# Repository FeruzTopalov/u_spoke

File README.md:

# u_spoke
uSpoke - headless Spoke

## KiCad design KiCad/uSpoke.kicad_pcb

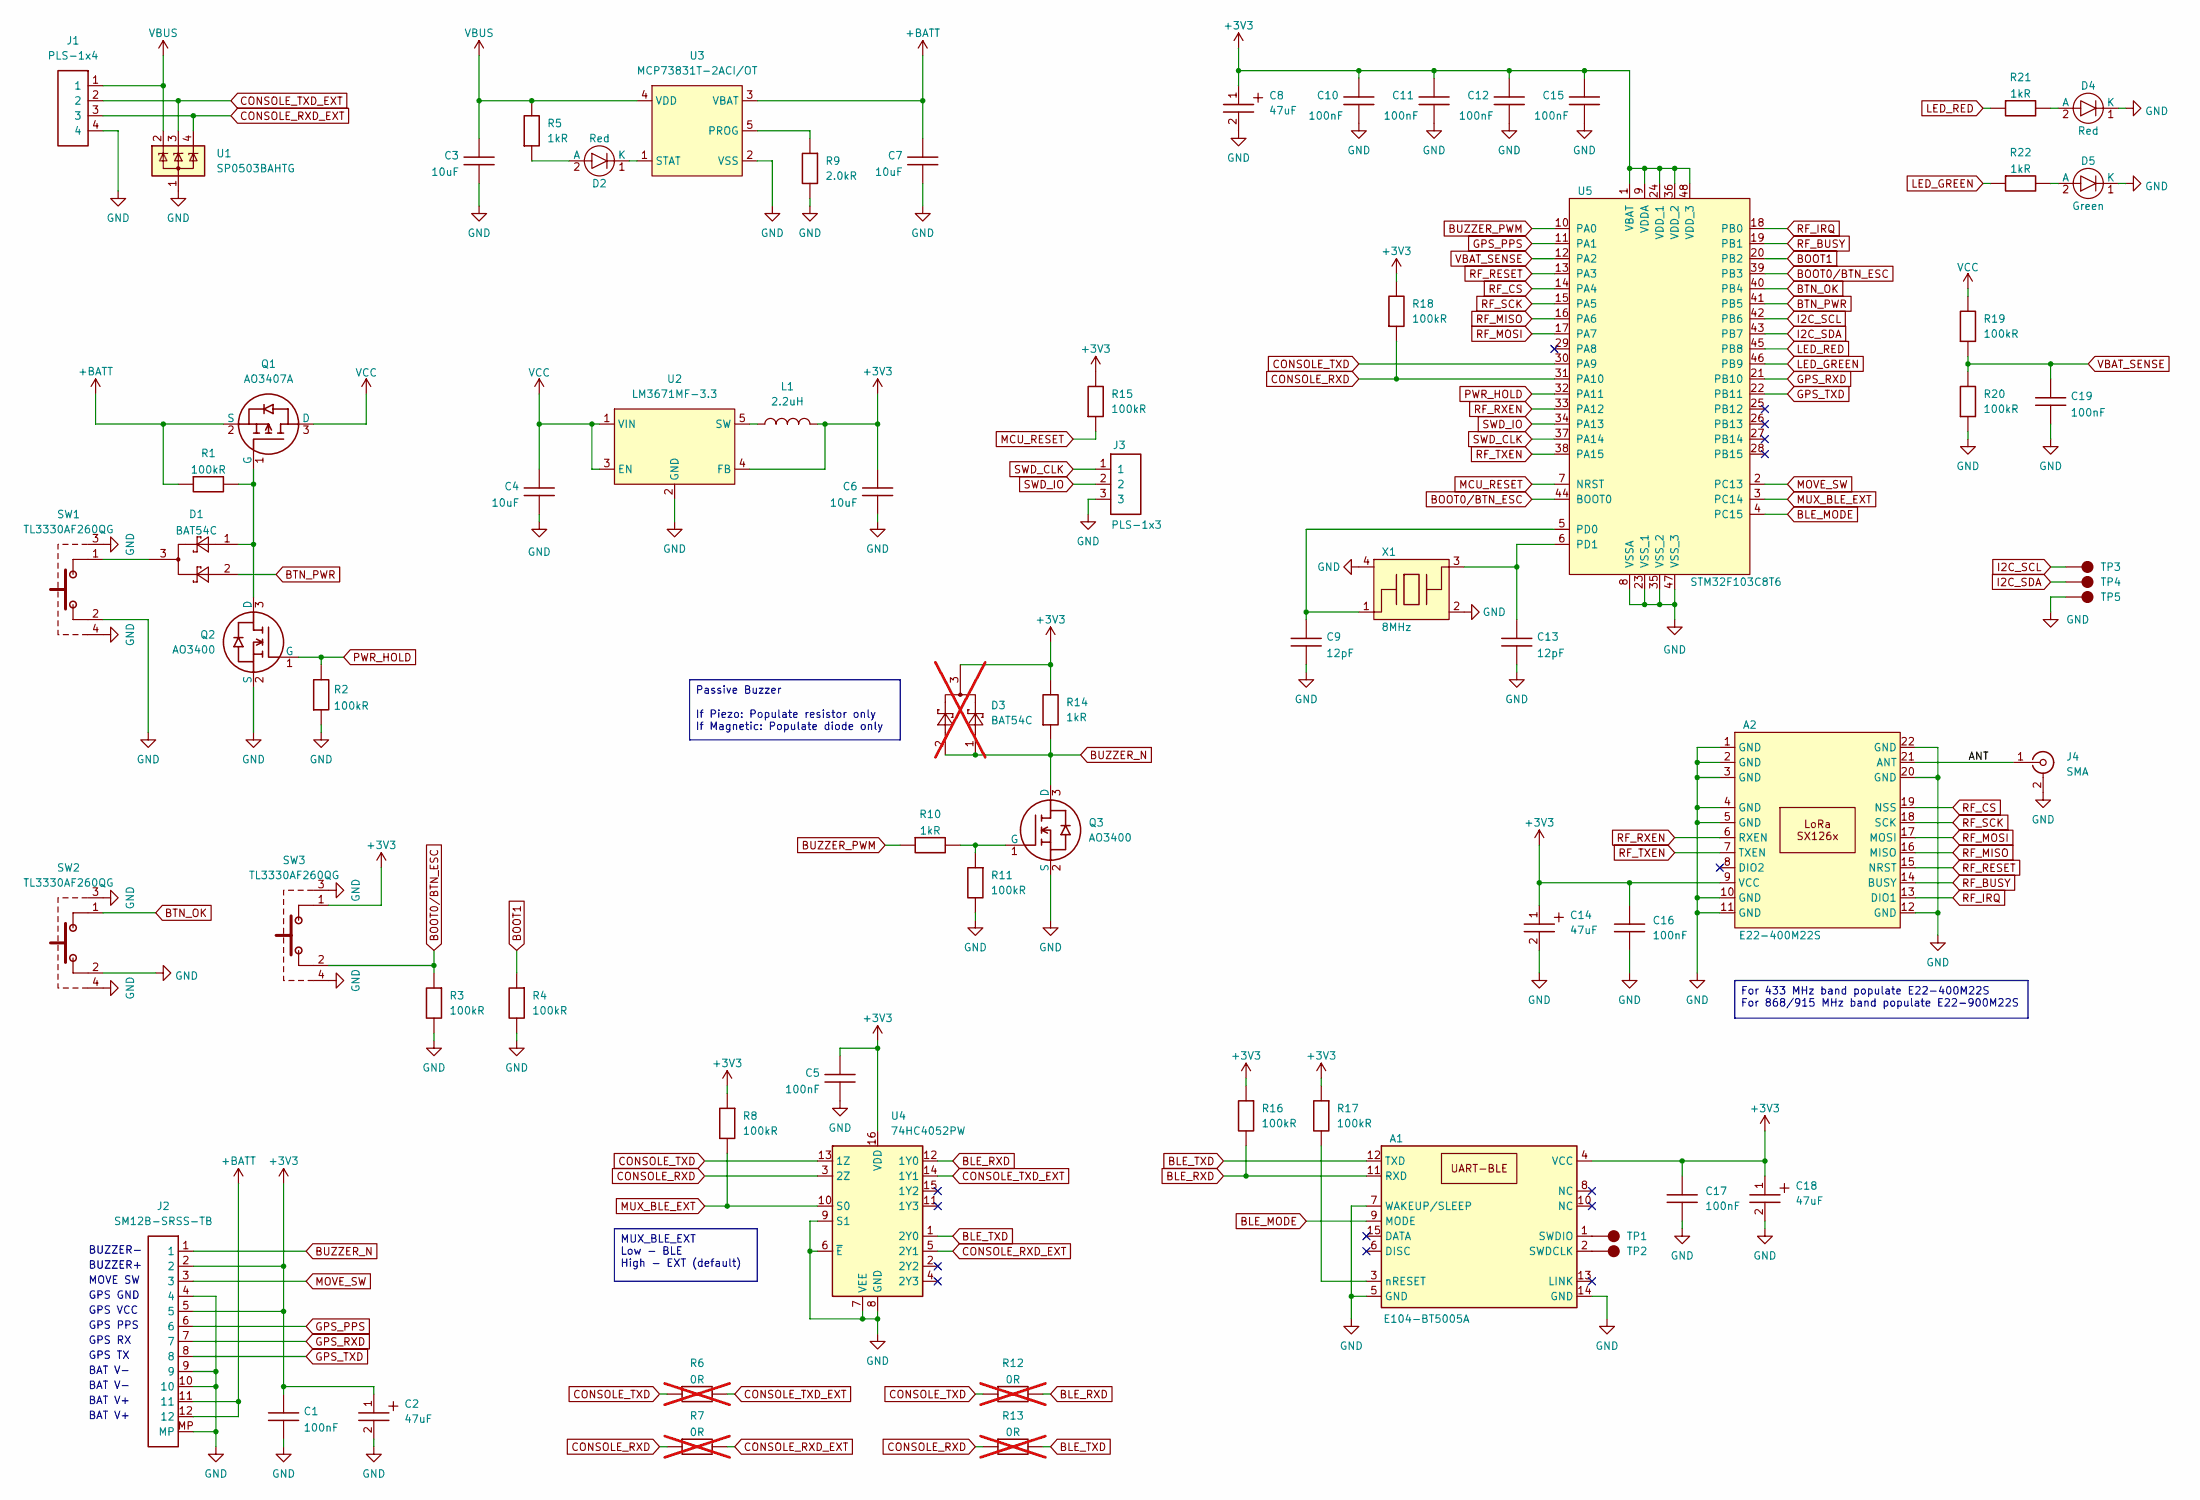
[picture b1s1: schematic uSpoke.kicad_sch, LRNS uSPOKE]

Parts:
A1: E104-BT5005A
A2: E22-400M22S; E22
C1, C5, C10, C11, C12, C15, C16, C17, C19: 100nF; C0603
C2, C8, C14, C18: 47uF; C_tantA
C3, C4, C6, C7: 10uF; C0805
C9, C13: 12pF; C0603
D1: BAT54C; SOT-23
D2, D4: Red; LED0603
D3: BAT54C; SOT-23; not fitted
D5: Green; LED0603
J1: PLS-1x4; Header_1x4
J2: SM12B-SRSS-TB
J3: PLS-1x3; Header_1x3
J4: SMA
L1: 2.2uH; L1616
Q1: AO3407A; SOT-23
Q2, Q3: AO3400; SOT-23
R1, R2, R3, R4, R8, R11, R15, R16, R17, R18, R19, R20: 100kR; R0603
R5, R10, R14, R21, R22: 1kR; R0603
R6, R7, R12, R13: 0R; R0603; not fitted
R9: 2.0kR; R0603
SW1, SW2, SW3: TL3330AF260QG
TP1, TP2, TP3, TP4, TP5: Pad-Round; Pad_round
U1: SP0503BAHTG; SOT-143
U2: LM3671MF-3.3; SOT-23-5
U3: MCP73831T-2ACI/OT; SOT-23-5
U4: 74HC4052PW; TSSOP-16
U5: STM32F103C8T6; LQFP-48
X1: 8MHz; Xtal_3225

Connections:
+3V3: A1.4 (VCC), A2.9 (VCC), C1.1, C2.1, C5.1, C6.2, C8.1, C10.1, C11.1, C12.1, C14.1, C15.1, C16.1, C17.1, C18.1, D3.3, J2.2, J2.5, L1.2, R8.1, R14.2, R15.2, R16.1, R17.1, R18.2, SW3.1, U2.4 (FB), U4.16 (VDD), U5.1 (VBAT), U5.9 (VDDA), U5.24 (VDD_1), U5.36 (VDD_2), U5.48 (VDD_3)
+BATT: C7.2, J2.11, J2.12, Q1.2 (S), R1.1, U3.3 (VBAT)
/ANT: A2.21 (ANT), J4.1 (RF)
BLE_MODE: A1.9 (MODE), U5.4 (PC15)
BLE_RXD: A1.11 (RXD), R12.2, R16.2, U4.12 (1Y0)
BLE_TXD: A1.12 (TXD), R13.2, U4.1 (2Y0)
BOOT0/BTN_ESC: R3.1, SW3.2, U5.39 (PB3), U5.44 (BOOT0)
BOOT1: R4.1, U5.20 (PB2)
BTN_OK: SW2.1, U5.40 (PB4)
BTN_PWR: D1.2, U5.41 (PB5)
BUZZER_N: D3.1, D3.2, J2.1, Q3.3 (D), R14.1
BUZZER_PWM: R10.1, U5.10 (PA0)
CONSOLE_RXD: R7.1, R13.1, R18.1, U4.3 (2Z), U5.31 (PA10)
CONSOLE_RXD_EXT: J1.3, R7.2, U1.4 (K), U4.5 (2Y1)
CONSOLE_TXD: R6.1, R12.1, U4.13 (1Z), U5.30 (PA9)
CONSOLE_TXD_EXT: J1.2, R6.2, U1.3 (K), U4.14 (1Y1)
GND: A1.5 (GND), A1.7 (WAKEUP/SLEEP), A1.14 (GND), A2.1 (GND), A2.2 (GND), A2.3 (GND), A2.4 (GND), A2.5 (GND), A2.10 (GND), A2.11 (GND), A2.12 (GND), A2.20 (GND), A2.22 (GND), C1.2, C2.2, C3.1, C4.1, C5.2, C6.1, C7.1, C8.2, C9.2, C10.2, C11.2, C12.2, C13.2, C14.2, C15.2, C16.2, C17.2, C18.2, C19.2, D4.1 (K), D5.1 (K), J1.4, J2.4, J2.9, J2.10, J2.MP, J3.3, J4.2 (GND), Q2.2 (S), Q3.2 (S), R2.1, R3.2, R4.2, R9.2, R11.2, R20.1, SW1.2, SW1.3 (1), SW1.4 (1), SW2.2, SW2.3 (1), SW2.4 (1), SW3.3 (1), SW3.4 (1), TP5.1, U1.1 (A), U2.2 (GND), U3.2 (VSS), U4.6 (~E), U4.7 (VEE), U4.8 (GND), U4.9 (S1), U5.8 (VSSA), U5.23 (VSS_1), U5.35 (VSS_2), U5.47 (VSS_3), X1.2, X1.4
GPS_PPS: J2.6, U5.11 (PA1)
GPS_RXD: J2.7, U5.21 (PB10)
GPS_TXD: J2.8, U5.22 (PB11)
I2C_SCL: TP3.1, U5.42 (PB6)
I2C_SDA: TP4.1, U5.43 (PB7)
LED_GREEN: R22.1, U5.46 (PB9)
LED_RED: R21.1, U5.45 (PB8)
MCU_RESET: R15.1, U5.7 (NRST)
MOVE_SW: J2.3, U5.2 (PC13)
MUX_BLE_EXT: R8.2, U4.10 (S0), U5.3 (PC14)
unnamed: A1.2 (SWDCLK), TP2.1
unnamed: A1.1 (SWDIO), TP1.1
unnamed: A1.3 (nRESET), R17.2
unnamed: D1.3, SW1.1
unnamed: D2.2 (A), R5.1
unnamed: D2.1 (K), U3.1 (STAT)
unnamed: D4.2 (A), R21.2
unnamed: D5.2 (A), R22.2
unnamed: D1.1, Q1.1 (G), Q2.3 (D), R1.2
unnamed: Q3.1 (G), R10.2, R11.1
unnamed: L1.1, U2.5 (SW)
unnamed: R9.1, U3.5 (PROG)
unnamed: C9.1, U5.5 (PD0), X1.1
unnamed: C13.1, U5.6 (PD1), X1.3
PWR_HOLD: Q2.1 (G), R2.2, U5.32 (PA11)
RF_BUSY: A2.14 (BUSY), U5.19 (PB1)
RF_CS: A2.19 (NSS), U5.14 (PA4)
RF_IRQ: A2.13 (DIO1), U5.18 (PB0)
RF_MISO: A2.16 (MISO), U5.16 (PA6)
RF_MOSI: A2.17 (MOSI), U5.17 (PA7)
RF_RESET: A2.15 (NRST), U5.13 (PA3)
RF_RXEN: A2.6 (RXEN), U5.33 (PA12)
RF_SCK: A2.18 (SCK), U5.15 (PA5)
RF_TXEN: A2.7 (TXEN), U5.38 (PA15)
SWD_CLK: J3.1, U5.37 (PA14)
SWD_IO: J3.2, U5.34 (PA13)
VBAT_SENSE: C19.1, R19.1, R20.2, U5.12 (PA2)
VBUS: C3.2, J1.1, R5.2, U1.2 (K), U3.4 (VDD)
VCC: C4.2, Q1.3 (D), R19.2, U2.1 (VIN), U2.3 (EN)

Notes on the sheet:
BAT V-
BAT V+
BUZZER+
GPS VCC
GPS GND
GPS RX
GPS TX
GPS PPS
BUZZER-
MOVE SW
Passive Buzzer If Piezo: Populate resistor only If Magnetic: Populate diode only
MUX_BLE_EXT Low - BLE High - EXT (default)
For 433 MHz band populate E22-400M22S For 868/915 MHz band populate E22-900M22S

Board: 2 copper layers, 70 parts (5 on the bottom side), 56 nets, no tracks yet.

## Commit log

2026-03-15 Update git ignore
2026-03-15 Copy Spoke HW 2.1 files
2026-03-15 Rename to uSpoke
2026-03-15 Clean SCH
2026-03-15 Clean PCB
2026-03-15 Arrangement
2026-03-30 Copy Spoke HW 2.1 files
    (cherry picked from commit 34f5f451f60d21dbebe338ec0545eddaf93c1f8e)
    # Conflicts:
    # KiCad/fp-lib-table
    # KiCad/sym-lib-table
2026-03-30 Revert "Copy Spoke HW 2.1 files"
    This reverts commit df39f7d8d0a30e85f8783cd0628c38681538e624.
2026-04-01 Rename to uSpoke
    (cherry picked from commit a0effae12703fde22e0195c2c61b714ac3e4bfb9)
    # Conflicts:
    # KiCad/uSpoke.kicad_pcb
    # KiCad/uSpoke.kicad_sch
2026-04-01 Remove not needed
2026-04-01 Remap GPS PPS and also (earlier) map BLE_MODE in place of ALARM_BTN
2026-04-02 Draft PCB
2026-04-03 Some progress
2026-04-09 Some PCB planning
2026-04-09 Clean up SCH
2026-04-10 Add 12P connector
2026-04-10 Add 1x4 header (magnetic pogo)
2026-04-10 Update SMA
2026-04-10 Replace charger IC
2026-04-10 Add 0603 led
2026-04-10 Add button
2026-04-10 Assign footprints
2026-04-10 Update PCB
2026-04-10 Color 12P conn
2026-04-11 Prettify SCH
2026-04-11 Fix ERC
2026-04-11 Clean SCH lib
2026-04-11 Update SCH and lib links
2026-04-11 Clean PCB lib
2026-04-11 Remove unused step files
2026-04-11 SCH to PCB sync
2026-04-11 Reduce footprints to auto soldering
2026-04-11 PCB comps placement
2026-04-11 Main placement done
2026-04-11 All placement done
